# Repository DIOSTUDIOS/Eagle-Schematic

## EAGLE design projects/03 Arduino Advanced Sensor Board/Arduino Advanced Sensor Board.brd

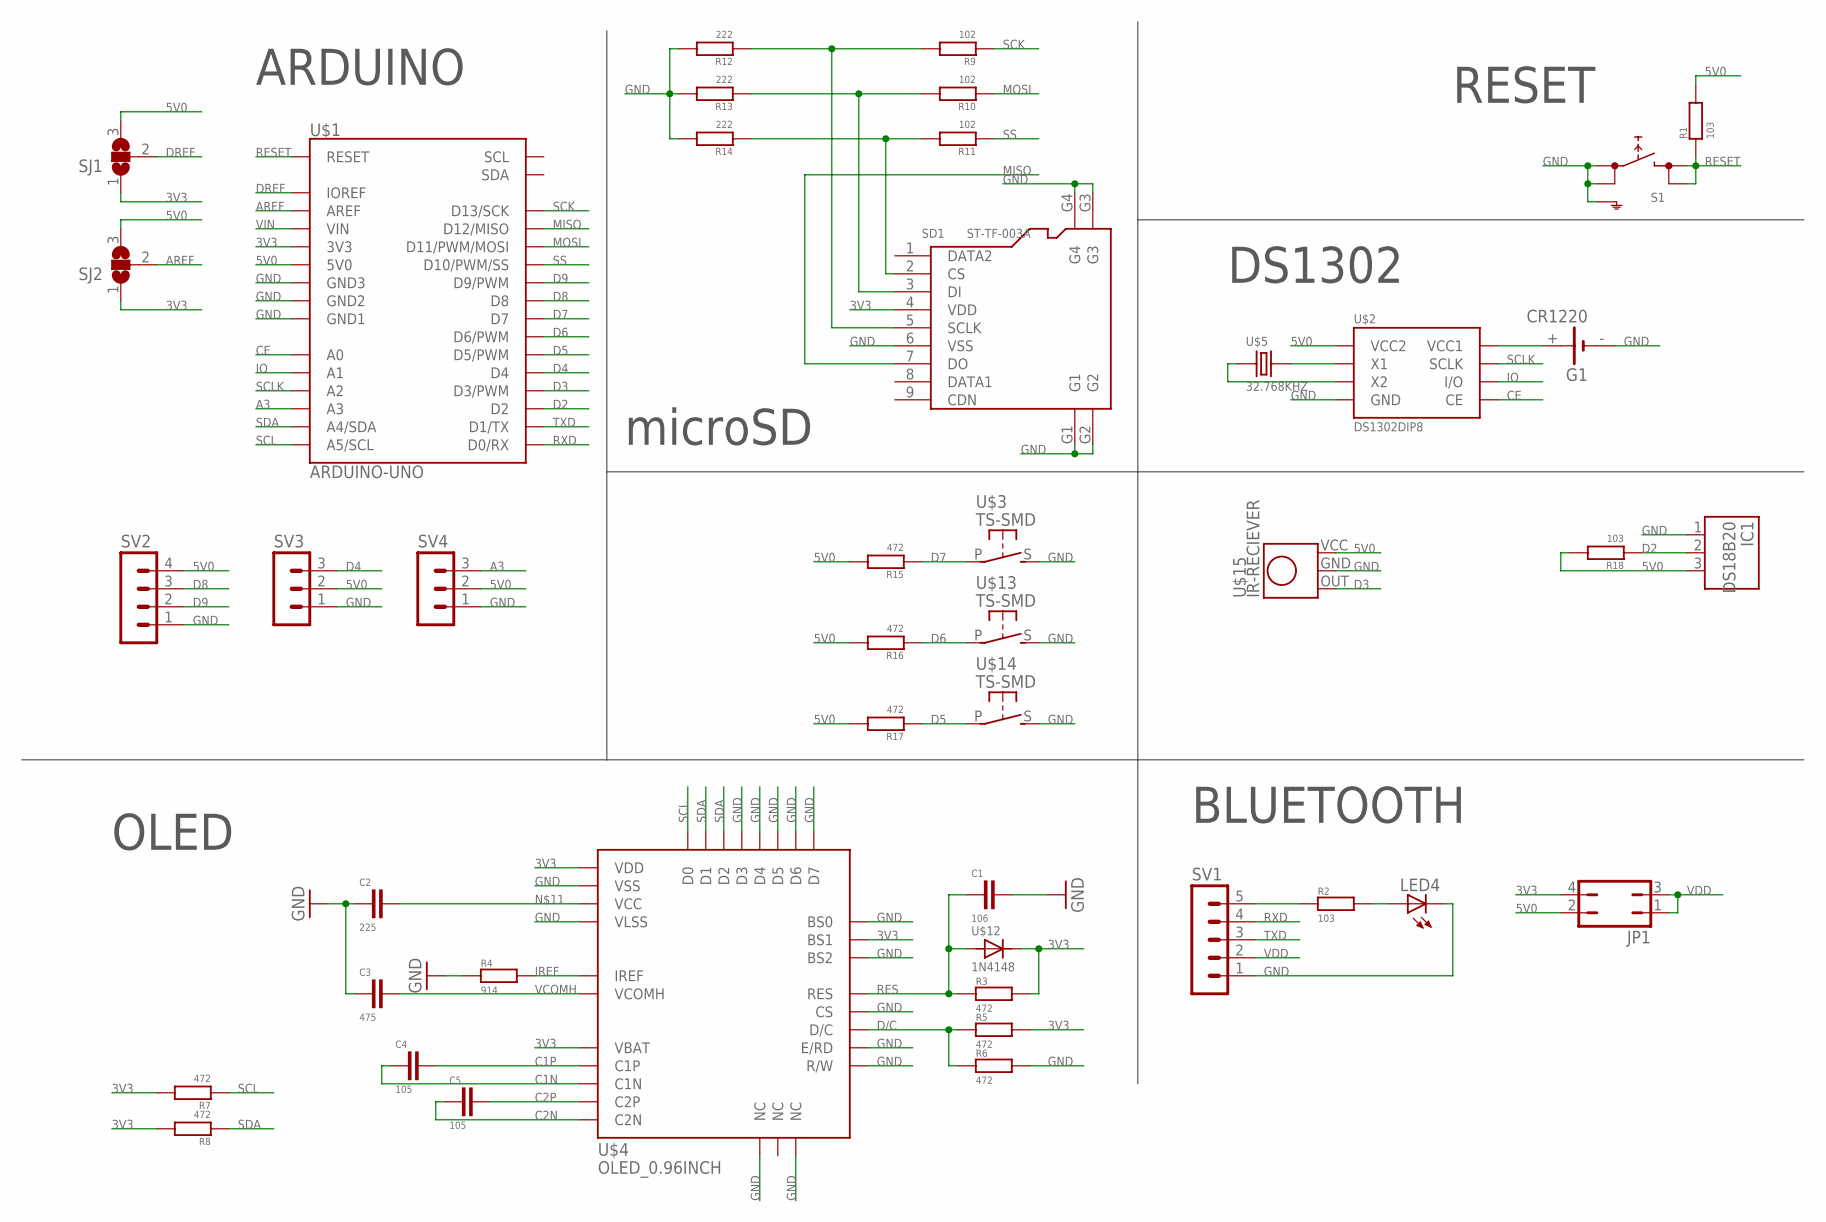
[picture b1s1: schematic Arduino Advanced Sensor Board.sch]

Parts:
C1: 106; C0805
C2: 225; C0805
C3: 475; C0805
C4, C5: 105; C0805
G1: CR1220
IC1: DS18B20; TO92
JP1: JP2Q
LED4: LEDCHIPLED_0805; LED0805
R1, R2, R18: 103; R0805
R3, R5, R6, R7, R8, R15, R16, R17: 472; R0805
R4: 914; R0805
R9, R10, R11: 102; R0805
R12, R13, R14: 222; R0805
S1: TS-SMD_6S6_SHIELD; TS-SMD_6*6_SHIELD
SD1: ST-TF-003A; MICRO-SD-SMD-9+4
SJ1, SJ2: SJ2W; SJ_2
SV1: MA05-1
SV2: MA04-1
SV3, SV4: MA03-1
U$1: ARDUINO-UNO
U$2: DS1302DIP8; DIP8
U$3, U$13, U$14: TS-SMD
U$4: OLED_0.96INCH
U$5: 32.768KHZ
U$12: 1N4148; SOD123
U$15: IR-RECIEVER

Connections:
3V3: JP1.4, R3.2, R5.2, R7.2, R8.2, SD1.4 (VDD), SJ1.1, SJ2.1, U$1.3V3, U$4.6 (VBAT), U$4.9 (VDD), U$4.11 (BS1), U$12.1
5V0: IC1.3 (VCC), JP1.2, R1.2, R15.2, R16.2, R17.2, R18.2, SJ1.3, SJ2.3, SV2.4, SV3.2, SV4.2, U$1.5V0, U$2.1 (VCC2), U$15.VCC
A3: SV4.3, U$1.A3
AREF: SJ2.2, U$1.AREF
C1N: C4.2, U$4.5 (C1N)
C1P: C4.1, U$4.4 (C1P)
C2N: C5.2, U$4.3 (C2N)
C2P: C5.1, U$4.2 (C2P)
CE: U$1.A0, U$2.5 (CE)
D2: IC1.2 (DQ), R18.1, U$1.D2
D3: U$1.D3 (D3/PWM), U$15.OUT
D4: SV3.3, U$1.D4
D5: R17.1, U$1.D5 (D5/PWM), U$14.P
D6: R16.1, U$1.D6 (D6/PWM), U$13.P
D7: R15.1, U$1.D7, U$3.P
D8: SV2.3, U$1.D8
D9: SV2.2, U$1.D9 (D9/PWM)
D/C: R5.1, R6.1, U$4.15 (D/C)
DREF: SJ1.2, U$1.REF (IOREF)
GND: C1.1, C2.2, C3.2, G1.-, IC1.1 (GND), LED4.C, R4.1, R6.2, R12.2, R13.2, R14.2, S1.1 (1.1), S1.2 (1.2), S1.5 (SH), SD1.6 (VSS), SD1.G1, SD1.G2, SD1.G3, SD1.G4, SV1.1, SV2.1, SV3.1, SV4.1, U$1.GND1, U$1.GND2, U$1.GND3, U$2.4 (GND), U$3.S, U$4.1 (NC), U$4.8 (VSS), U$4.10 (BS0), U$4.12 (BS2), U$4.13 (CS), U$4.16 (R/W), U$4.17 (E/RD), U$4.21 (D3), U$4.22 (D4), U$4.23 (D5), U$4.24 (D6), U$4.25 (D7), U$4.29 (VLSS), U$4.30 (NC), U$13.S, U$14.S, U$15.GND
IO: U$1.A1, U$2.6 (I/O)
IREF: R4.2, U$4.26 (IREF)
MISO: SD1.7 (DO), U$1.D12 (D12/MISO)
MOSI: R10.1, U$1.D11 (D11/PWM/MOSI)
unnamed: U$2.2 (X1), U$5.P$2 (2)
unnamed: U$2.3 (X2), U$5.P$1 (1)
unnamed: G1.+, U$2.8 (VCC1)
unnamed: R2.1, SV1.5
unnamed: LED4.A, R2.2
unnamed: R11.2, R14.1, SD1.2 (CS)
unnamed: R10.2, R13.1, SD1.3 (DI)
unnamed: C2.1, U$4.28 (VCC)
unnamed: R9.2, R12.1, SD1.5 (SCLK)
RES: C1.2, R3.1, U$4.14 (RES), U$12.2
RESET: R1.1, S1.3 (2.1), S1.4 (2.2), U$1.RST (RESET)
RXD: SV1.4, U$1.D0 (D0/RX)
SCK: R9.1, U$1.D13 (D13/SCK)
SCL: R7.1, U$1.A5 (A5/SCL), U$4.18 (D0)
SCLK: U$1.A2, U$2.7 (SCLK)
SDA: R8.1, U$1.A4 (A4/SDA), U$4.19 (D1), U$4.20 (D2)
SS: R11.1, U$1.D10 (D10/PWM/SS)
TXD: SV1.3, U$1.D1 (D1/TX)
VCOMH: C3.1, U$4.27 (VCOMH)
VDD: JP1.1, JP1.3, SV1.2
VIN: U$1.VIN

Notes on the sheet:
OLED
DS1302
BLUETOOTH
RESET
ARDUINO
microSD

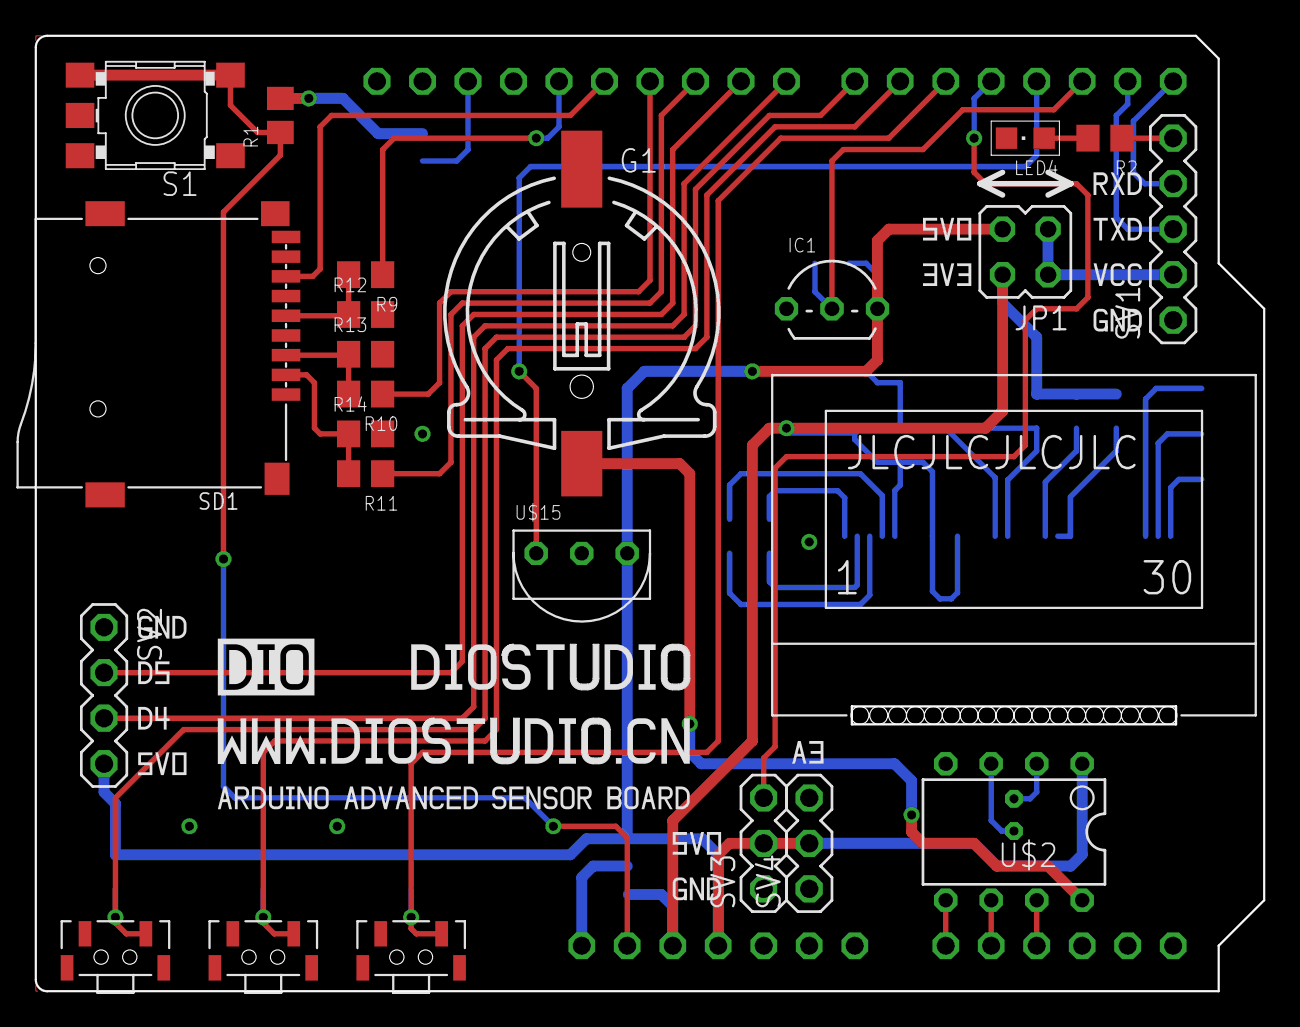
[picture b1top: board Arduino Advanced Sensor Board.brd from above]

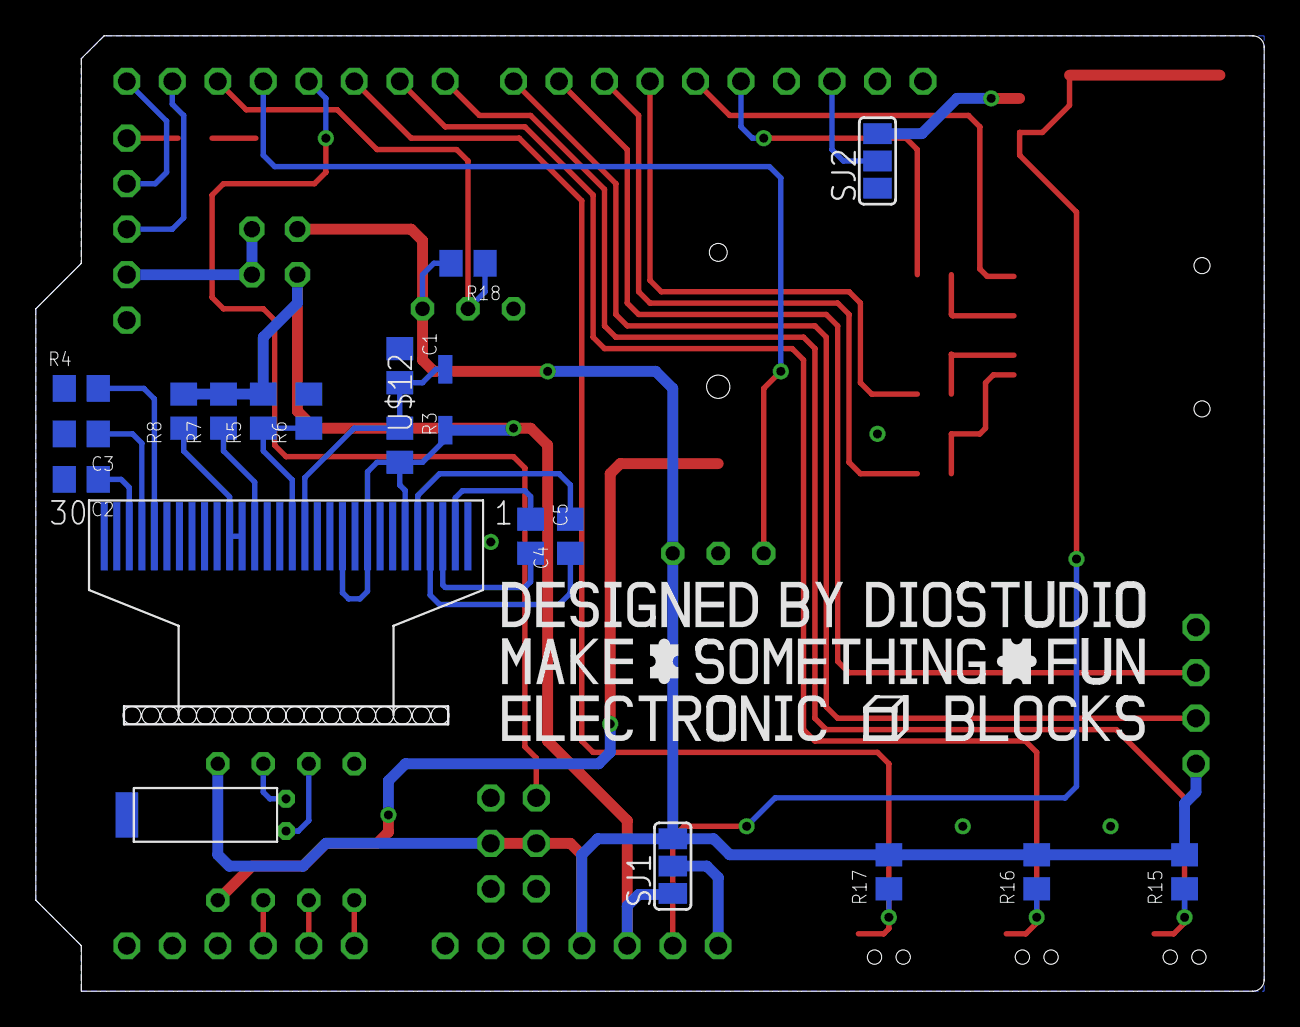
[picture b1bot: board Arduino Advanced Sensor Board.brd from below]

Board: 2 copper layers, 68.5 x 53.2 mm, 62 parts (20 on the bottom side), 44 nets.

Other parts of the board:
U$6, U$21, U$26: 5V0_050
U$7: 3V3_050
U$8, U$22, U$25: GND_050
U$9: RXD_050
U$10: TXD_050
U$11: VCC_050
U$16: ARDUINO_ADVANCED_SENSOR_BOARD
U$17: MAKE_SOMETHING_FUN_100
U$18: LOGO_100
U$19: DIOSTUDIO_100
U$20: WWW.DIOSTUDIO.CN_100
U$24: A3_050
U$27: D5_050
U$28: D4_050

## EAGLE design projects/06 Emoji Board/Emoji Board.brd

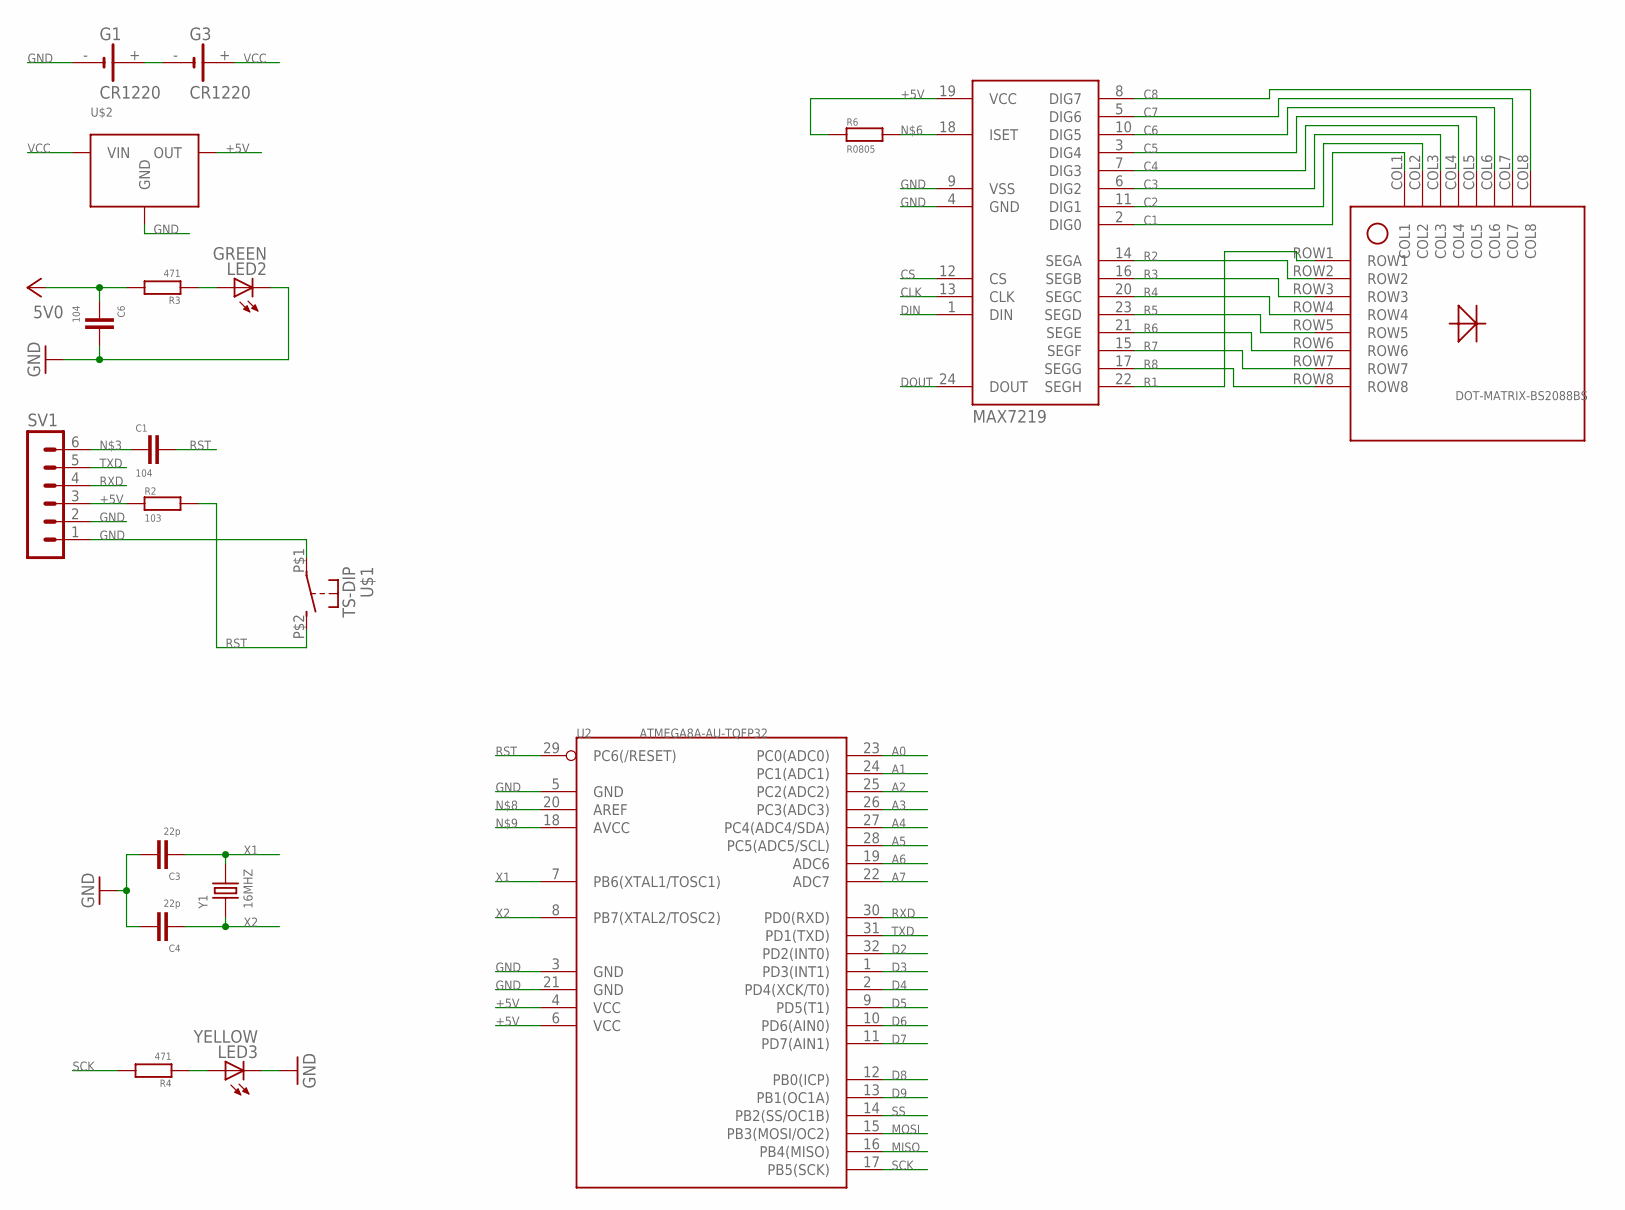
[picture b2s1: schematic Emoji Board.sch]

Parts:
C1, C6: 104; C0805
C3, C4: 22p; C0805
G1, G3: CR1220
L2: DOT-MATRIX-BS2088BS; 2088BS
LED2: GREEN; CHIPLED_0805
LED3: YELLOW; CHIPLED_0805
M2: MAX7219; SOP24
R2: 103; R0805
R3, R4: 471; R0805
R6: R0805
SV1: MA06-1
U2: ATMEGA8A-AU-TQFP32; TQFP32
U$1: TS-DIP
U$2: AMS1117-5V0SOT22; SOT223
Y1: 16MHZ; HC49US

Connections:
+5V: C6.2, M2.19 (VCC), R2.1, R3.2, R6.1, SV1.3, U2.4 (VCC), U2.6 (VCC), U$2.OUT
A0: U2.23 (PC0(ADC0))
A1: U2.24 (PC1(ADC1))
A2: U2.25 (PC2(ADC2))
A3: U2.26 (PC3(ADC3))
A4: U2.27 (PC4(ADC4/SDA))
A5: U2.28 (PC5(ADC5/SCL))
A6: U2.19 (ADC6)
A7: U2.22 (ADC7)
C1: L2.COL1, M2.2 (DIG0)
C2: L2.COL2, M2.11 (DIG1)
C3: L2.COL3, M2.6 (DIG2)
C4: L2.COL4, M2.7 (DIG3)
C5: L2.COL5, M2.3 (DIG4)
C6: L2.COL6, M2.10 (DIG5)
C7: L2.COL7, M2.5 (DIG6)
C8: L2.COL8, M2.8 (DIG7)
CLK: M2.13 (CLK)
CS: M2.12 (CS)
D2: U2.32 (PD2(INT0))
D3: U2.1 (PD3(INT1))
D4: U2.2 (PD4(XCK/T0))
D5: U2.9 (PD5(T1))
D6: U2.10 (PD6(AIN0))
D7: U2.11 (PD7(AIN1))
D8: U2.12 (PB0(ICP))
D9: U2.13 (PB1(OC1A))
DIN: M2.1 (DIN)
DOUT: M2.24 (DOUT)
GND: C3.1, C4.1, C6.1, G1.-, LED2.C, LED3.C, M2.4 (GND), M2.9 (VSS), SV1.1, SV1.2, U2.3 (GND), U2.5 (GND), U2.21 (GND), U$1.P$1, U$2.GND
MISO: U2.16 (PB4(MISO))
MOSI: U2.15 (PB3(MOSI/OC2))
unnamed: LED3.A, R4.1
unnamed: G1.+, G3.-
unnamed: C1.2, SV1.6
unnamed: M2.18 (ISET), R6.2
unnamed: LED2.A, R3.1
R1: L2.ROW1, M2.22 (SEGH)
R2: L2.ROW2, M2.14 (SEGA)
R3: L2.ROW3, M2.16 (SEGB)
R4: L2.ROW4, M2.20 (SEGC)
R5: L2.ROW5, M2.23 (SEGD)
R6: L2.ROW6, M2.21 (SEGE)
R7: L2.ROW7, M2.15 (SEGF)
R8: L2.ROW8, M2.17 (SEGG)
RST: C1.1, R2.2, U2.29 (PC6(/RESET)), U$1.P$2 (S)
RXD: SV1.4, U2.30 (PD0(RXD))
SCK: R4.2, U2.17 (PB5(SCK))
SS: U2.14 (PB2(SS/OC1B))
TXD: SV1.5, U2.31 (PD1(TXD))
VCC: G3.+, U$2.VIN
X1: C3.2, U2.7 (PB6(XTAL1/TOSC1)), Y1.2
X2: C4.2, U2.8 (PB7(XTAL2/TOSC2)), Y1.1

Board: 2 copper layers, 19 parts (0 on the bottom side), 30 nets, no tracks yet.

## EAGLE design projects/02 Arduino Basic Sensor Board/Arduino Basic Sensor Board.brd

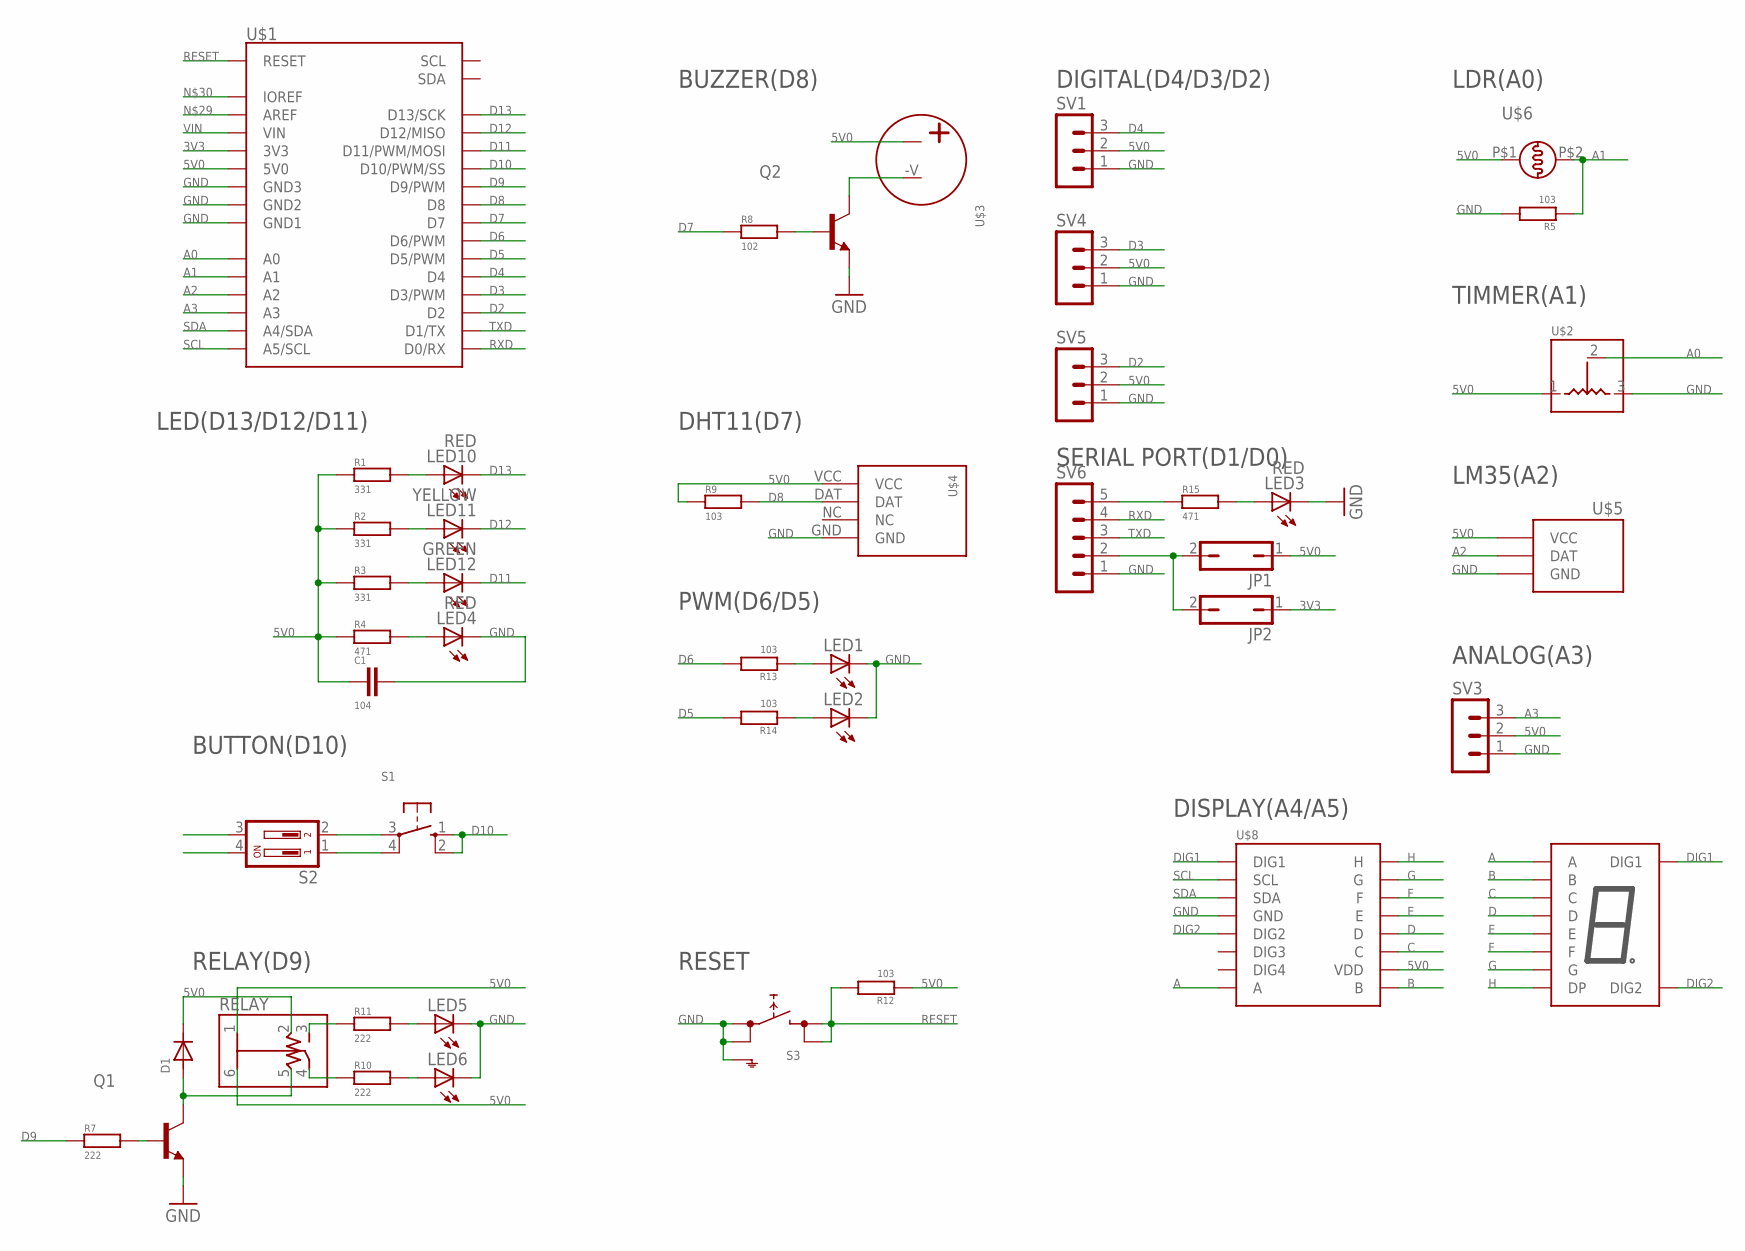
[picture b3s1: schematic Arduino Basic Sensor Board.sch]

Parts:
C1: 104; C0805
D1: DIODESMB; SMB
JP1, JP2: JP1Q
LED1, LED2: LEDCHIPLED_1206; LED1206
LED3, LED4: RED; LED0805
LED5, LED6: LEDSML1206; SML1206
LED10: RED; SML1206
LED11: YELLOW; SML1206
LED12: GREEN; SML1206
Q1, Q2: S8050SOT23; SOT23
R1, R2, R3: 331; R0805
R4, R15: 471; R0805
R5, R9, R12, R13, R14: 103; R0805
R7, R10, R11: 222; R0805
R8: 102; R0805
RELAY: RELAY-HK4100F-DC5V
S1: TS-DIP-4.54.5; TS-DIP-4.5*4.5
S2: SD4-02
S3: TS-SMD_6S6_SHIELD; TS-SMD_6*6_SHIELD
SV1, SV3, SV4, SV5: MA03-1
SV6: MA05-1
U$1: ARDUINO-UNO
U$2: 33623362; 3362
U$3: BUZZER
U$4: DHT11
U$5: LM35; TO92
U$6: LDR
U$8: TM1650; SOP16
U$15: 3261AS; TN_AS_2_0.36INCH

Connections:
3V3: JP2.1, U$1.3V3
5V0: C1.2, D1.1, JP1.1, R1.1, R2.1, R3.1, R4.1, R9.1, R12.1, RELAY.1, RELAY.2, RELAY.6, SV1.2, SV3.2, SV4.2, SV5.2, U$1.5V0, U$2.1, U$3.+V, U$4.VCC, U$5.1 (VCC), U$6.P$1, U$8.10 (VDD)
A: U$8.8 (A), U$15.3 (A)
A0: U$1.A0, U$2.2
A1: R5.1, U$1.A1, U$6.P$2
A2: U$1.A2, U$5.2 (DAT)
A3: SV3.3, U$1.A3
B: U$8.9 (B), U$15.9 (B)
C: U$8.11 (C), U$15.8 (C)
D: U$8.12 (D), U$15.6 (D)
D2: SV5.3, U$1.D2
D3: SV4.3, U$1.D3 (D3/PWM)
D4: SV1.3, U$1.D4
D5: R14.2, U$1.D5 (D5/PWM)
D6: R13.2, U$1.D6 (D6/PWM)
D7: R8.1, U$1.D7
D8: R9.2, U$1.D8, U$4.DAT
D9: R7.1, U$1.D9 (D9/PWM)
D10: S1.1 (S), S1.2 (S1), U$1.D10 (D10/PWM/SS)
D11: LED12.C, U$1.D11 (D11/PWM/MOSI)
D12: LED11.C, U$1.D12 (D12/MISO)
D13: LED10.C, U$1.D13 (D13/SCK)
DIG1: U$8.1 (DIG1), U$15.10 (DIG1)
DIG2: U$8.5 (DIG2), U$15.5 (DIG2)
E: U$8.13 (E), U$15.7 (E)
F: U$8.14 (F), U$15.4 (F)
G: U$8.15 (G), U$15.1 (G)
GND: C1.1, LED1.C, LED2.C, LED3.C, LED4.C, LED5.C, LED6.C, Q1.E, Q2.E, R5.2, S3.1 (1.1), S3.2 (1.2), S3.5 (SH), SV1.1, SV3.1, SV4.1, SV5.1, SV6.1, U$1.GND1, U$1.GND2, U$1.GND3, U$2.3, U$4.GND, U$5.3 (GND), U$8.4 (GND)
H: U$8.16 (H), U$15.2 (DP)
unnamed: LED10.A, R1.2
unnamed: LED11.A, R2.2
unnamed: LED12.A, R3.2
unnamed: LED4.A, R4.2
unnamed: S1.4 (P1), S2.1
unnamed: S1.3, S2.2
unnamed: LED1.A, R13.1
unnamed: R10.1, RELAY.4
unnamed: R11.1, RELAY.3
unnamed: LED6.A, R10.2
unnamed: LED5.A, R11.2
unnamed: LED2.A, R14.1
unnamed: JP1.2, JP2.2, SV6.2
unnamed: R15.1, SV6.5
unnamed: LED3.A, R15.2
unnamed: D1.2, Q1.C, RELAY.5
unnamed: Q1.B, R7.2
unnamed: Q2.B, R8.2
unnamed: Q2.C, U$3.-V
RESET: R12.2, S3.3 (2.1), S3.4 (2.2), U$1.RST (RESET)
RXD: SV6.4, U$1.D0 (D0/RX)
SCL: U$1.A5 (A5/SCL), U$8.2 (SCL)
SDA: U$1.A4 (A4/SDA), U$8.3 (SDA)
TXD: SV6.3, U$1.D1 (D1/TX)
VIN: U$1.VIN

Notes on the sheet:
LED(D13/D12/D11)
BUTTON(D10)
RELAY(D9)
SERIAL PORT(D1/D0)
DHT11(D7)
BUZZER(D8)
ANALOG(A3)
LM35(A2)
TIMMER(A1)
LDR(A0)
PWM(D6/D5)
DIGITAL(D4/D3/D2)
RESET
DISPLAY(A4/A5)

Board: 2 copper layers, 46 parts (0 on the bottom side), 53 nets, no tracks yet.

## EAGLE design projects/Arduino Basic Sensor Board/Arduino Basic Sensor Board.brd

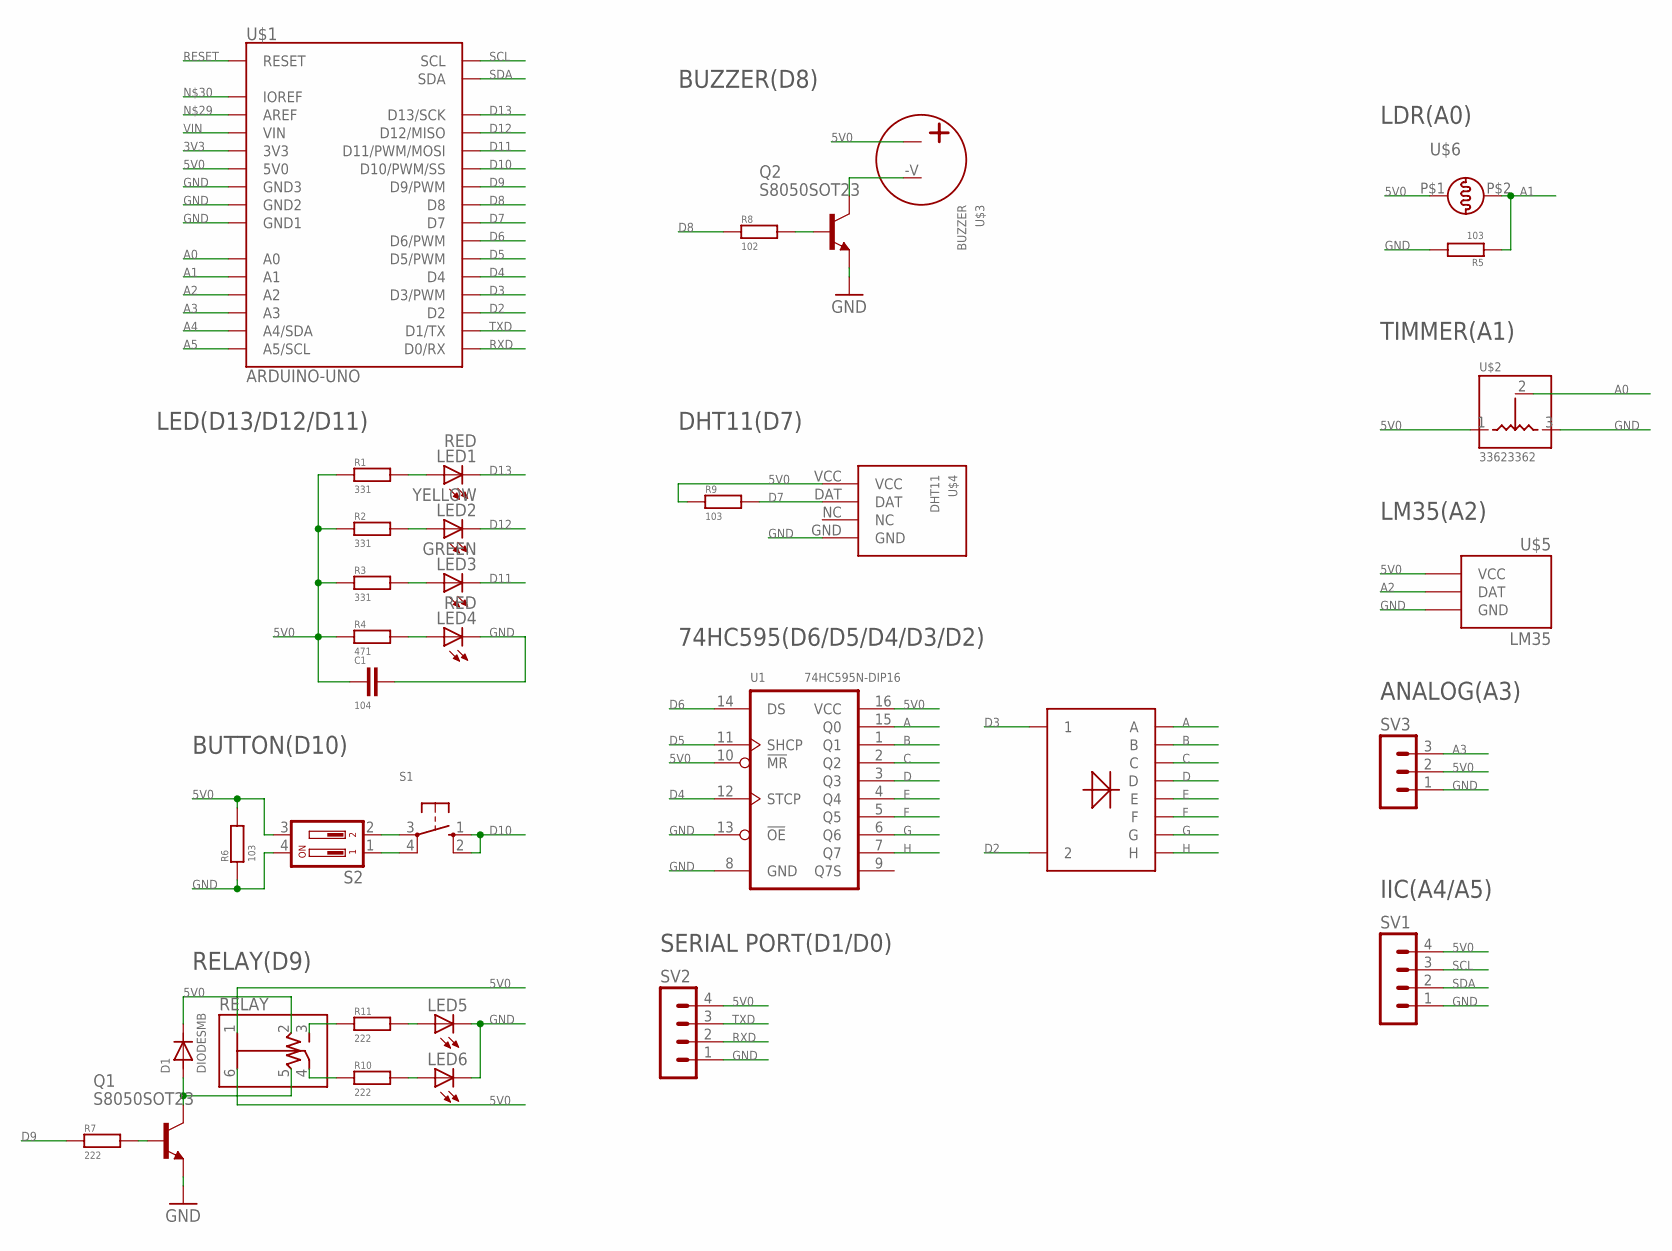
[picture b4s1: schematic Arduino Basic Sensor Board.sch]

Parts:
C1: 104; C0805
D1: DIODESMB; SMB
LED1: RED; LED2X5
LED2: YELLOW; LED2X5
LED3: GREEN; LED2X5
LED4: RED; LED0805
LED5, LED6: LEDSML1206; SML1206
Q1, Q2: S8050SOT23; SOT23
R1, R2, R3: 331; R0805
R4: 471; R0805
R5, R6, R9: 103; R0805
R7, R10, R11: 222; R0805
R8: 102; R0805
RELAY: RELAY-HK4100F-DC5V
S1: TS-DIP-4.54.5; TS-DIP-4.5*4.5
S2: SD4-02
SV1, SV2: MA04-1
SV3: MA03-1
U1: 74HC595N-DIP16; DIP16-2.54-20.32X5.84MM
U$1: ARDUINO-UNO
U$2: 33623362; 3362
U$3: BUZZER
U$4: DHT11
U$5: LM35; TO92
U$6: LDR
U$8: LG3622BH

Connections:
3V3: U$1.3V3
5V0: C1.2, D1.1, R1.1, R2.1, R3.1, R4.1, R6.2, R9.1, RELAY.1, RELAY.2, RELAY.6, S2.3, SV1.4, SV2.4, SV3.2, U1.10 (!MR), U1.16 (VCC), U$1.5V0, U$2.1, U$3.+V, U$4.VCC, U$5.1 (VCC), U$6.P$1
A: U1.15 (Q0), U$8.A
A0: U$1.A0, U$2.2
A1: R5.1, U$1.A1, U$6.P$2
A2: U$1.A2, U$5.2 (DAT)
A3: SV3.3, U$1.A3
A4: U$1.A4 (A4/SDA)
A5: U$1.A5 (A5/SCL)
B: U1.1 (Q1), U$8.B
C: U1.2 (Q2), U$8.C
D: U1.3 (Q3), U$8.D
D2: U$1.D2, U$8.2
D3: U$1.D3 (D3/PWM), U$8.1
D4: U1.12 (STCP), U$1.D4
D5: U1.11 (SHCP), U$1.D5 (D5/PWM)
D6: U1.14 (DS), U$1.D6 (D6/PWM)
D7: R9.2, U$1.D7, U$4.DAT
D8: R8.1, U$1.D8
D9: R7.1, U$1.D9 (D9/PWM)
D10: S1.1 (S), S1.2 (S1), U$1.D10 (D10/PWM/SS)
D11: LED3.K (C), U$1.D11 (D11/PWM/MOSI)
D12: LED2.K (C), U$1.D12 (D12/MISO)
D13: LED1.K (C), U$1.D13 (D13/SCK)
E: U1.4 (Q4), U$8.E
F: U1.5 (Q5), U$8.F
G: U1.6 (Q6), U$8.G
GND: C1.1, LED4.C, LED5.C, LED6.C, Q1.E, Q2.E, R5.2, R6.1, S2.4, SV1.1, SV2.1, SV3.1, U1.8 (GND), U1.13 (!OE), U$1.GND1, U$1.GND2, U$1.GND3, U$2.3, U$4.GND, U$5.3 (GND)
H: U1.7 (Q7), U$8.H
unnamed: LED1.A, R1.2
unnamed: LED2.A, R2.2
unnamed: LED3.A, R3.2
unnamed: LED4.A, R4.2
unnamed: S1.4 (P1), S2.1
unnamed: S1.3, S2.2
unnamed: R10.1, RELAY.4
unnamed: R11.1, RELAY.3
unnamed: LED6.A, R10.2
unnamed: LED5.A, R11.2
unnamed: D1.2, Q1.C, RELAY.5
unnamed: Q1.B, R7.2
unnamed: Q2.B, R8.2
unnamed: Q2.C, U$3.-V
RESET: U$1.RST (RESET)
RXD: SV2.2, U$1.D0 (D0/RX)
SCL: SV1.3, U$1.SCL
SDA: SV1.2, U$1.SDA
TXD: SV2.3, U$1.D1 (D1/TX)
VIN: U$1.VIN

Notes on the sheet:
LED(D13/D12/D11)
BUTTON(D10)
RELAY(D9)
SERIAL PORT(D1/D0)
74HC595(D6/D5/D4/D3/D2)
DHT11(D7)
BUZZER(D8)
IIC(A4/A5)
ANALOG(A3)
LM35(A2)
TIMMER(A1)
LDR(A0)

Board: 2 copper layers, 56 parts (8 on the bottom side), 44 nets, no tracks yet.

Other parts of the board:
U$7, U$25, U$26: 5V0_050
U$9: GREEN_050
U$10: ARDUINO_BASIC_SENSOR_BOARD_050
U$13: POWER_050
U$14: RED_050
U$15: YELLOW_050
U$16: SCL_050
U$17, U$19, U$24: GND_050
U$18: RXD_050
U$20: TXD_050
U$21: HIGH_050
U$22: LOW_050
U$23: SDA_050
U$27: A3_050
U$28: LOGO_100
U$29: DIOSTUDIO_100
U$30: WWW.DIOSTUDIO.CN_100

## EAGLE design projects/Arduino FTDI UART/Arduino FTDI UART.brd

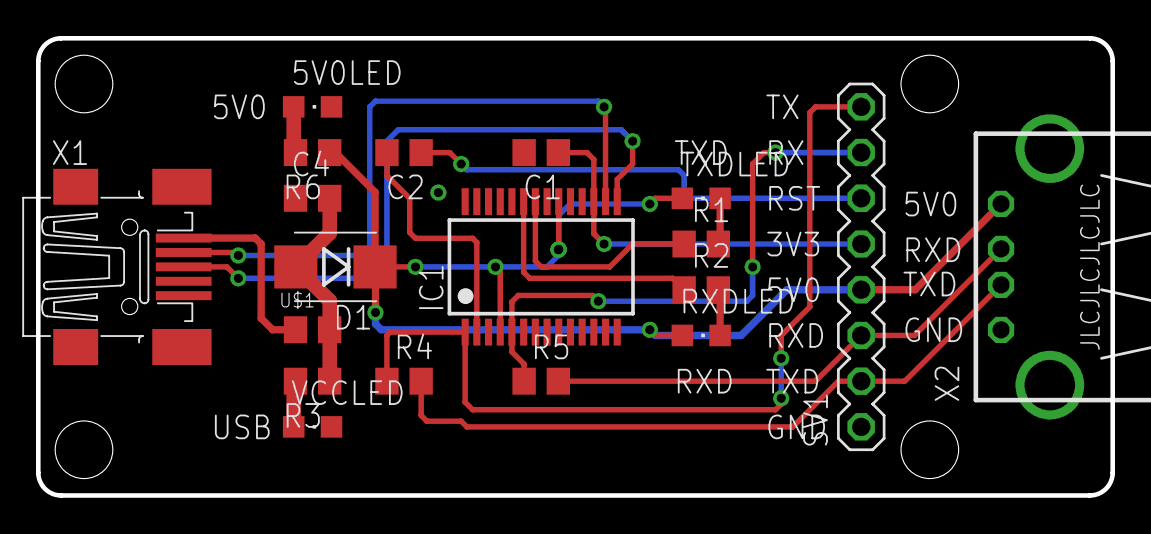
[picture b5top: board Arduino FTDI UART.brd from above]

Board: 2 copper layers, 59.7 x 25.4 mm, 19 parts (0 on the bottom side), 19 nets.

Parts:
5V0LED: RED; CHIPLED_0805
C1, C2, C4: 104; C0805
D1: DIODESMB; SMB
IC1: FT232RL; SSOP28
R1, R2: 331; R0805
R3, R6: 471; R0805
R4, R5: 102; R0805
RXDLED: YELLOW; CHIPLED_0805
SV1: MA08-1
TXDLED: YELLOW; CHIPLED_0805
U$1: FUSE0805; F0805
VCCLED: RED; CHIPLED_0805
X1: MINI-USB; 32005-201
X2: USB-A-SHIELD

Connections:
+3V3: C1.1, IC1.17, SV1.5
+5V: D1.1, IC1.4, IC1.20, R6.1, RXDLED.A, SV1.4, TXDLED.A, X2.4
DM: IC1.16, X1.2
DP: IC1.15, X1.3
GND: 5V0LED.C, C1.2, C4.1, IC1.7, IC1.18, IC1.21, IC1.25, IC1.26, SV1.1, VCCLED.C, X1.5, X2.1, X2.S1, X2.S2
unnamed: R2.2, RXDLED.C
unnamed: U$1.1, X1.1
unnamed: R1.2, TXDLED.C
unnamed: R3.2, VCCLED.A
unnamed: C2.2, IC1.2
unnamed: 5V0LED.A, R6.2
RESET: C2.1, SV1.6
RX: IC1.5, R5.1, SV1.7
RXD: R5.2, SV1.3, X2.3
RXDLED: IC1.23, R2.1
TX: IC1.1, R4.1, SV1.8
TXD: R4.2, SV1.2, X2.2
TXDLED: IC1.22, R1.1
VCC: C4.2, D1.2, R3.1, U$1.2

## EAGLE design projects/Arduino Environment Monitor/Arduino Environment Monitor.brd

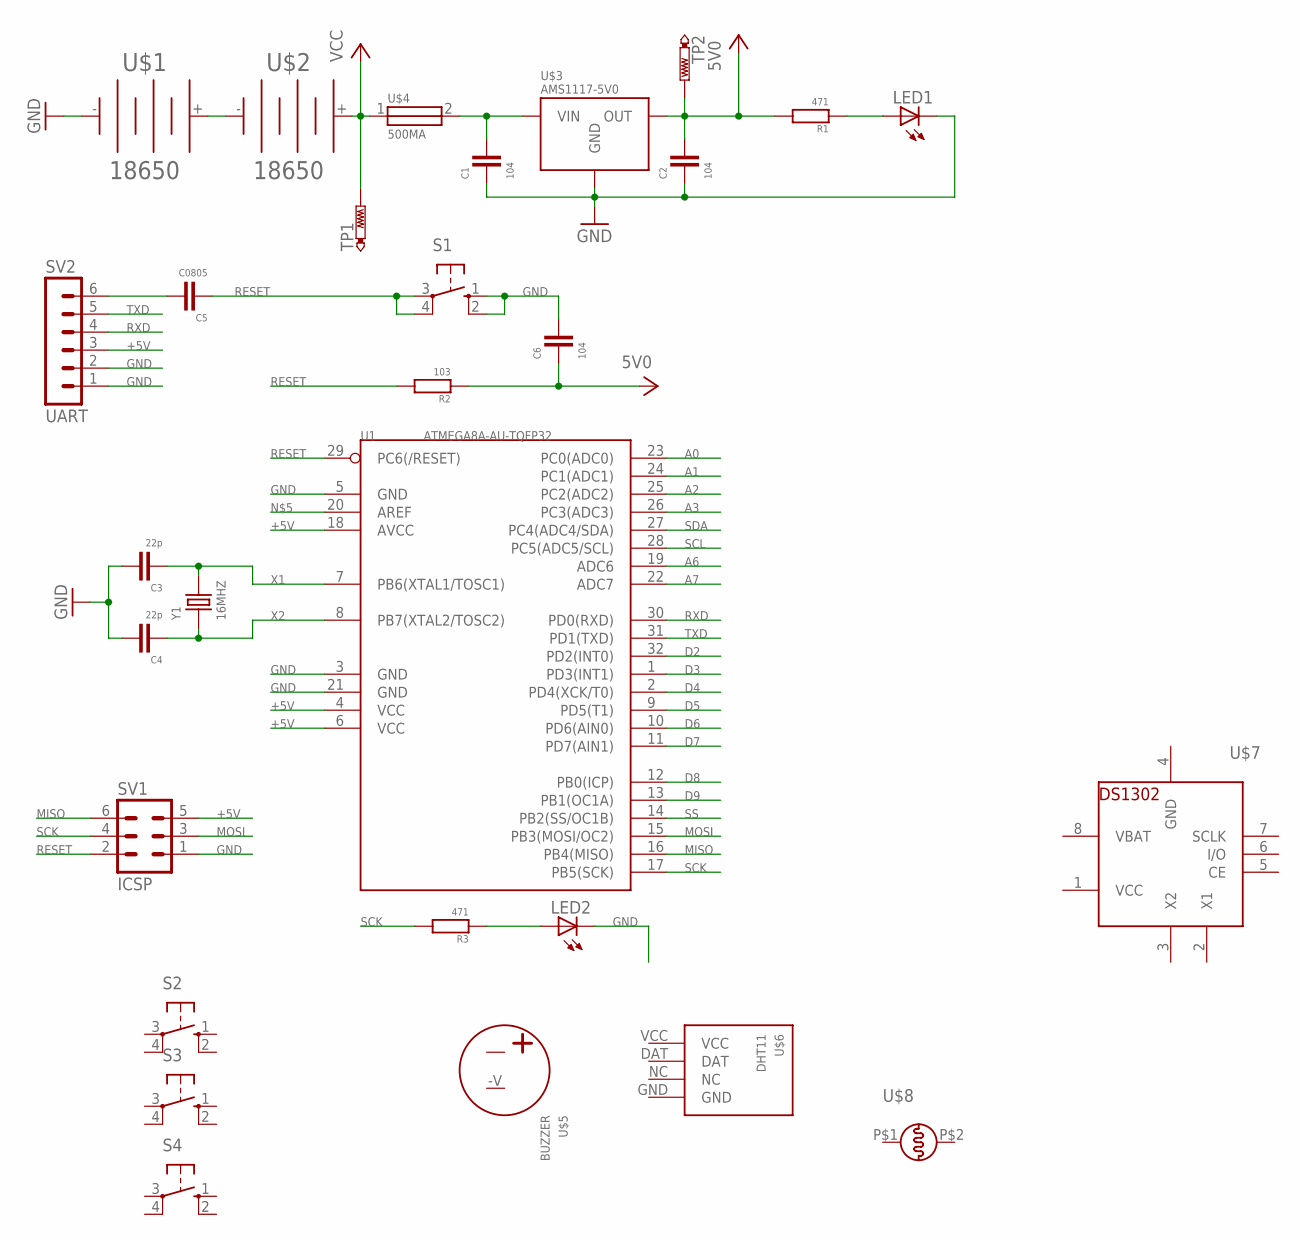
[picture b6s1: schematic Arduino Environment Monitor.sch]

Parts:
C1, C2, C6: 104; C0805
C3, C4: 22p; CDIP
C5: C0805
LED1, LED2: LED3MM
R1, R3: 471; RDIP
R2: 103; RDIP
S1: 10-XX; B3F-10XX
S2, S3, S4: 40-XX; B3F-40XX
SV1: ICSP; MA03-2
SV2: UART; MA06-1
TP1, TP2: TEST-PADB1,27; B1,27
U1: ATMEGA8A-AU-TQFP32; TQFP32-0.8-7X7MM
U$1, U$2: 18650; 18650-SMD
U$3: AMS1117-5V0; SOT223
U$4: 500MA; F0805
U$5: BUZZER
U$6: DHT11
U$7: DS1302; DIL08-ROUND
U$8: LDR
Y1: 16MHZ; HC49US

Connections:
+5V: C2.1, C6.2, R1.P$2 (2), R2.P$1 (1), SV1.5, SV2.3, TP2.TP, U1.4 (VCC), U1.6 (VCC), U1.18 (AVCC), U$3.OUT
A0: U1.23 (PC0(ADC0))
A1: U1.24 (PC1(ADC1))
A2: U1.25 (PC2(ADC2))
A3: U1.26 (PC3(ADC3))
A6: U1.19 (ADC6)
A7: U1.22 (ADC7)
D2: U1.32 (PD2(INT0))
D3: U1.1 (PD3(INT1))
D4: U1.2 (PD4(XCK/T0))
D5: U1.9 (PD5(T1))
D6: U1.10 (PD6(AIN0))
D7: U1.11 (PD7(AIN1))
D8: U1.12 (PB0(ICP))
D9: U1.13 (PB1(OC1A))
GND: C1.2, C2.2, C3.P$1 (1), C4.P$1 (1), C6.1, LED1.K (C), LED2.K (C), S1.1 (S), S1.2 (S1), SV1.1, SV2.1, SV2.2, U1.3 (GND), U1.5 (GND), U1.21 (GND), U$1.-, U$3.GND, U$7.4 (GND)
MISO: SV1.6, U1.16 (PB4(MISO))
MOSI: SV1.3, U1.15 (PB3(MOSI/OC2))
unnamed: U$1.+, U$2.-
unnamed: C1.1, U$3.VIN, U$4.2
unnamed: C5.1, SV2.6
unnamed: LED1.A, R1.P$1 (1)
unnamed: LED2.A, R3.P$1 (1)
RESET: C5.2, R2.P$2 (2), S1.3, S1.4 (P1), SV1.2, U1.29 (PC6(/RESET))
RXD: SV2.4, U1.30 (PD0(RXD))
SCK: R3.P$2 (2), SV1.4, U1.17 (PB5(SCK))
SCL: U1.28 (PC5(ADC5/SCL))
SDA: U1.27 (PC4(ADC4/SDA))
SS: U1.14 (PB2(SS/OC1B))
TXD: SV2.5, U1.31 (PD1(TXD))
VBAT: U$7.8 (VBAT)
VCC: TP1.TP, U$2.+, U$4.1, U$7.1 (VCC)
X1: C3.P$2 (2), U1.7 (PB6(XTAL1/TOSC1)), Y1.2
X2: C4.P$2 (2), U1.8 (PB7(XTAL2/TOSC2)), Y1.1

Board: 2 copper layers, 29 parts (0 on the bottom side), 16 nets, no tracks yet.

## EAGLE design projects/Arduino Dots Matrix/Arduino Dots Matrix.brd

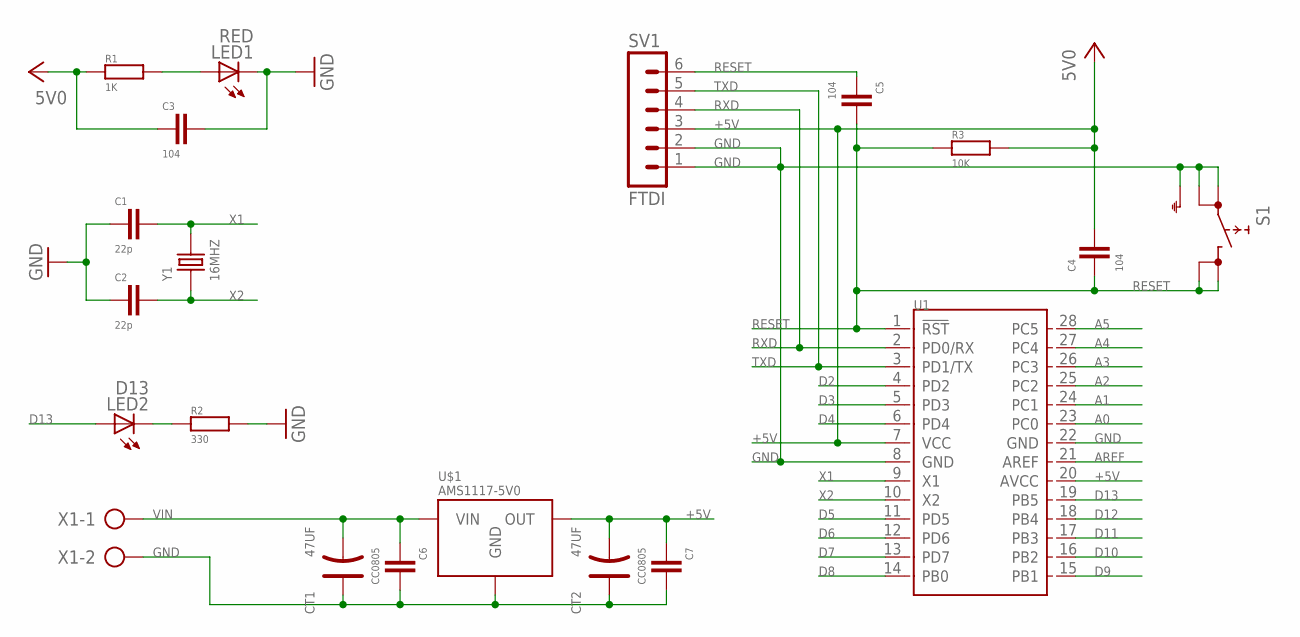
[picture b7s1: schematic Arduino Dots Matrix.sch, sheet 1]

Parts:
C1, C2: 22p; C0805
C3, C4, C5: 104; C0805
C6, C7: CC0805; C0805
CT1, CT2: 47UF; ELECTRO-SMD-C-6MM
LED1: RED; CHIPLED_0805
LED2: D13; CHIPLED_0805
R1: 1K; R0805
R2: 330; R0805
R3: 10K; R0805
S1: SKHMPSE010; SKHMPXE010
SV1: FTDI; MA06-1
U1: MCU-ATMEGA328P-PU(DIP28); DIP28-2.54-35.6X13.5MM
U$1: AMS1117-5V0; SOT223
X1: AK500/2
Y1: 16MHZ; HC49US

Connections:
+5V: C3.2, C4.1, C7.2, CT2.-, R1.1, R3.2, SV1.3, U1.7 (VCC), U1.20 (AVCC), U$1.OUT; also elsewhere on the board
A0: U1.23 (PC0)
A1: U1.24 (PC1)
A2: U1.25 (PC2)
A3: U1.26 (PC3)
A4: U1.27 (PC4)
A5: U1.28 (PC5)
AREF: U1.21 (AREF)
D2: U1.4 (PD2)
D3: U1.5 (PD3)
D4: U1.6 (PD4)
D5: U1.11 (PD5)
D6: U1.12 (PD6)
D7: U1.13 (PD7)
D8: U1.14 (PB0)
D9: U1.15 (PB1)
D10: U1.16 (PB2)
D11: U1.17 (PB3)
D12: U1.18 (PB4)
D13: LED2.A, U1.19 (PB5)
GND: C1.2, C2.2, C3.1, C6.1, C7.1, CT1.+, CT2.+, LED1.C, R2.2, S1.1 (1.1), S1.2 (1.2), S1.5 (SH), SV1.1, SV1.2, U1.8 (GND), U1.22 (GND), U$1.GND, X1.2; also elsewhere on the board
unnamed: LED1.A, R1.2
unnamed: LED2.C, R2.1
RESET: C4.2, C5.1, C5.2, R3.1, S1.3 (2.1), S1.4 (2.2), SV1.6, U1.1 (!RST)
RXD: SV1.4, U1.2 (PD0/RX)
TXD: SV1.5, U1.3 (PD1/TX)
VIN: C6.2, CT1.-, U$1.VIN, X1.1
X1: C1.1, U1.9 (X1), Y1.2
X2: C2.1, U1.10 (X2), Y1.1
